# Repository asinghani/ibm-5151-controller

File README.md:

# IBM 5151 Controller

Building a VT100 emulator out of an old IBM 5151 monitor and an FPGA

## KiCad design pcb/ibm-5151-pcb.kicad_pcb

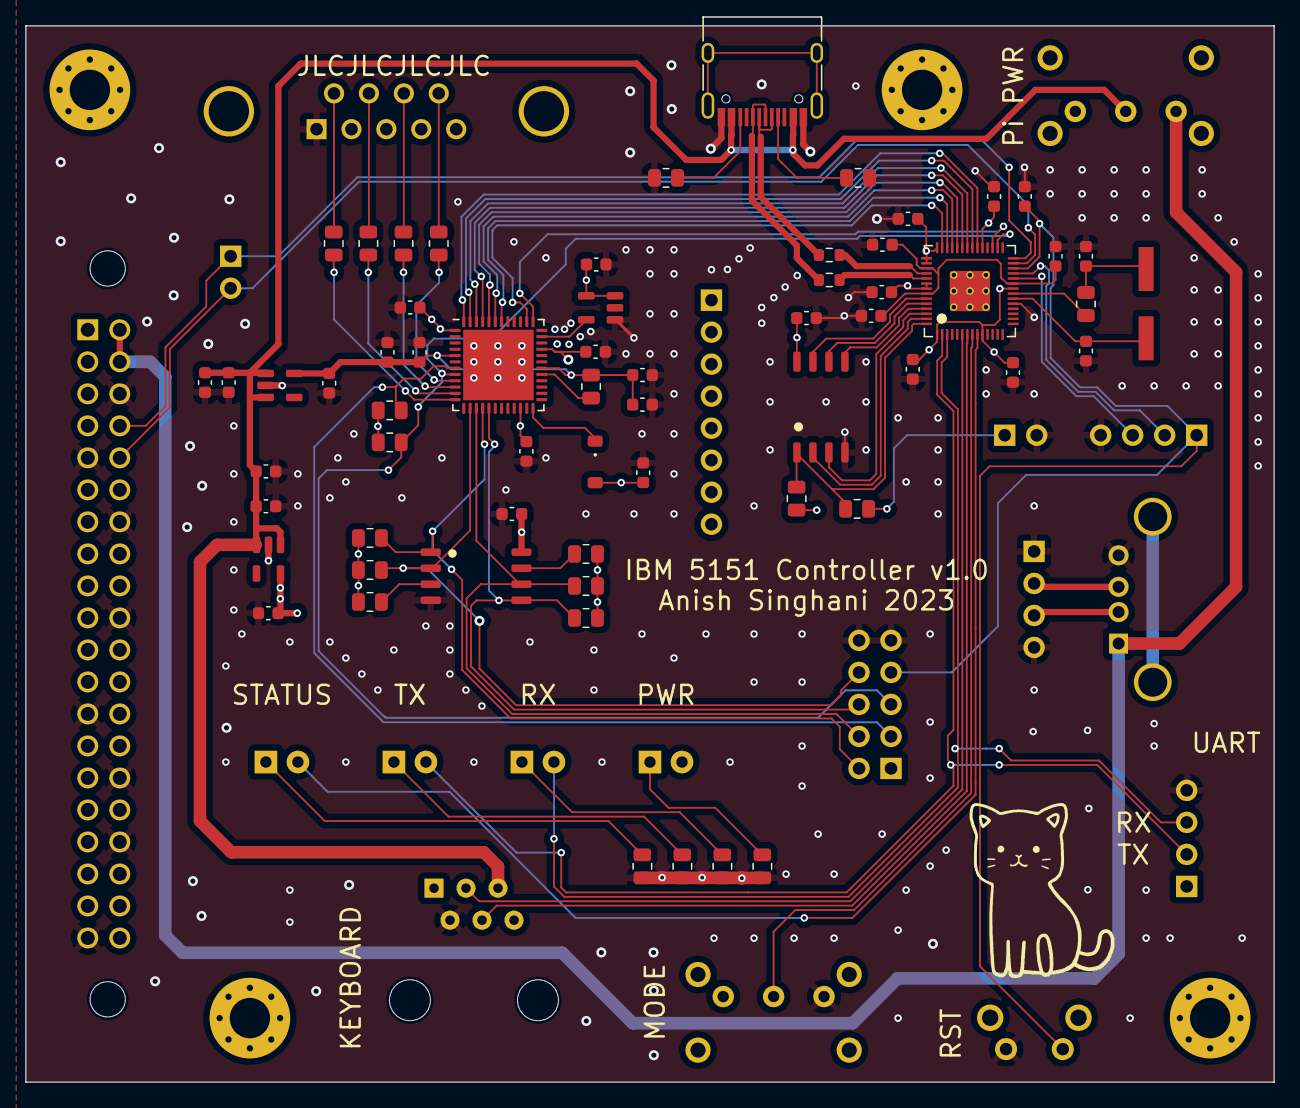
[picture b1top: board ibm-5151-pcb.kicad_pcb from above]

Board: 4 copper layers, 99.1 x 83.8 mm, 84 parts (0 on the bottom side), 67 nets.

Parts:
C1, C2, C13: 10u; C_0603_1608Metric
C3, C4, C5, C6, C22, C26: 1u; C_0603_1608Metric
C7, C8, C9, C10, C11, C12, C15, C16, C20, C21, C23, C24, C25, C27, C28: 100n; C_0603_1608Metric
C14: 10n; C_0603_1608Metric
C17, C18: 27p; C_0603_1608Metric
C19: 0.1u; C_0603_1608Metric
D1: MBR130; D_SOD-123
D2: RXLED; LED_D5.0mm
D3: TXLED; LED_D5.0mm
D4: STLED; LED_D5.0mm
D5: PWRLED; LED_D5.0mm
H1, H2, H3, H4: MountingHole; MountingHole_3.2mm_M3_Pad_Via
IC1: Raspberry Pi Zero W; RASPBERRYPIZEROWV13
J2: USB_USER; USB_C_Receptacle_HRO_TYPE-C-31-M-12
J3: BOOT; PinHeader_1x02_P2.54mm_Vertical
J4: RP_DEBUG; PinHeader_1x04_P2.54mm_Vertical
J5: FPGA_IF_TP; PinHeader_1x08_P2.54mm_Vertical
J6: UART_HDR; PinSocket_1x04_P2.54mm_Horizontal
J7: KBD_CONN; RJ12_Amphenol_54601
J8: DE9_Receptacle; DSUB-9_Female_Horizontal_P2.77x2.84mm_EdgePinOffset7.70mm_H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
J9: NET_DBG; PinHeader_1x02_P2.54mm_Vertical
J10: USB_A; USB_A_Molex_67643_Horizontal
J11: USB_HDR; PinHeader_1x04_P2.54mm_Vertical
J12: FPGA_DEBUG; PinHeader_2x05_P2.54mm_Vertical
R1, R2, R3, R4, R5, R6: 10K; R_0805_2012Metric
R7, R8: 2K2; R_0805_2012Metric
R9, R21, R22, R23: 10R; R_0805_2012Metric
R10, R11: 5K1; R_0805_2012Metric
R12, R14, R17, R18, R19, R20: 1k; R_0805_2012Metric
R13: 10k, DNF; R_0805_2012Metric
R15, R16: 27R; R_0603_1608Metric
R24: 100R; R_0805_2012Metric
SW1: RP_RST; SW_Tactile_SPST_Angled_PTS645Vx58-2LFS
SW2, SW3: SW_SPDT; SW_E-Switch_EG1224_SPDT_Angled
U1: MIC5504-1.2YM5; SOT-23-5
U2: MIC5504-3.3YM5; SOT-23-5
U3: W25Q32JVSS; SOIC-8_5.23x5.23mm_P1.27mm
U4: W25Q128JVS; SOIC-8_5.23x5.23mm_P1.27mm
U5: ICE40UP5K-SG48ITR; QFN-48-1EP_7x7mm_P0.5mm_EP5.6x5.6mm
U6: RP2040; RP2040-QFN-56
X1: SiT2001BI-S2-33E-12.000000G; SOT-23-5
Y1: ECS-120-20-3X-TR; XTAL_ECS-120-20-3X-TR

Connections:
+1V2: C5.1, C12.1, C13.1, C14.1, C15.1, R24.2, U1.5 (VOUT), U5.5 (VCC), U5.30 (VCC)
+3V3: C6.1, C7.2, C8.1, C9.1, C10.1, C11.1, C16.1, C23.1, C24.1, C25.1, C26.1, C27.1, C28.2, D1.2 (A), D5.2 (A), J6.1, J12.1, R1.1, R2.1, R3.1, R4.1, R5.1, R6.1, R7.1, R8.1, R13.1, SW2.1 (A), U2.5 (VOUT), U3.8 (VCC), U4.8 (VCC), U5.1 (VCCIO_2), U5.22 (SPI_VCCIO1), U5.33 (VCCIO_0), U6.1 (IOVDD), U6.10 (IOVDD), U6.22 (IOVDD), U6.33 (IOVDD), U6.42 (IOVDD), U6.43 (ADC_AVDD), U6.44 (VREG_IN), U6.48 (USB_VDD), U6.49 (IOVDD), X1.3 (OE), X1.4 (Vcc)
+5V: C1.1, C2.1, C3.1, C4.1, J2.A4 (VBUS), J2.A9 (VBUS), J2.B4 (VBUS), J2.B9 (VBUS), J7.5, SW3.2 (B), U1.1 (VIN), U1.3 (EN), U2.1 (VIN), U2.3 (EN)
FPGA_CSn: J12.2, R1.2, U3.1 (~CS), U5.16 (IOB_35b_SPI_SS)
FPGA_DONE: J12.3, R8.2, U5.7 (CDONE)
FPGA_IF_0: J5.1, U5.48 (IOB_4a), U6.34 (GPIO22)
FPGA_IF_1: J5.2, U5.47 (IOB_2a), U6.35 (GPIO23)
FPGA_IF_2: J5.3, U5.46 (IOB_0a), U6.36 (GPIO24)
FPGA_IF_3: J5.4, U5.45 (IOB_5b), U6.37 (GPIO25)
FPGA_IF_4: J5.5, U5.44 (IOB_3b_G6), U6.38 (GPIO26_ADC0)
FPGA_IF_5: J5.6, U5.43 (IOT_49a), U6.39 (GPIO27_ADC1)
FPGA_IF_6: J5.7, U5.42 (IOT_51a), U6.40 (GPIO28_ADC2)
FPGA_IF_7: J5.8, U5.38 (IOT_50b), U6.41 (GPIO29_ADC3)
FPGA_IF_RST: U5.37 (IOT_45a_G1), U6.31 (GPIO20)
FPGA_MISO: J12.8, R4.2, U3.2 (DO(IO1)), U5.14 (IOB_32a_SPI_SO)
FPGA_MOSI: J12.6, R3.2, U3.5 (DI(IO0)), U5.17 (IOB_33b_SPI_SI)
FPGA_OSC: U5.35 (IOT_46b_G0), X1.5 (OUT)
FPGA_RSTn: J12.5, R7.2, U5.8 (~CRESET), U6.30 (GPIO19)
FPGA_SCK: J12.4, R2.2, U3.6 (CLK), U5.15 (IOB_34a_SPI_SCK)
GND: C1.2, C2.2, C3.2, C4.2, C5.2, C6.2, C7.1, C8.2, C9.2, C10.2, C11.2, C12.2, C13.2, C14.2, C15.2, C16.2, C17.2, C18.2, C19.2, C20.2, C21.2, C22.2, C23.2, C24.2, C25.2, C26.2, C27.2, C28.1, IC1.6 (GND_1), IC1.9 (GND_2), IC1.14 (GND_3), IC1.20 (GND_4), IC1.25 (GND_5), IC1.30 (GND_6), IC1.34 (GND_7), IC1.39 (GND_8), J2.A1 (GND), J2.A12 (GND), J2.B1 (GND), J2.B12 (GND), J3.2, J4.4, J6.4, J7.2, J8.1, J8.2, J10.4 (GND), J11.1, J11.4, J12.9, J12.10, R10.2, R11.2, R17.2, R18.2, R19.2, R20.2, SW1.2, SW2.3 (C), U1.2 (GND), U2.2 (GND), U3.4 (GND), U4.4 (GND), U5.49 (GND), U6.19 (TESTEN), U6.57 (GND), X1.1 (GND)
KBD_RX: J7.4, U6.7 (GPIO5)
KBD_TX: J7.3, U6.6 (GPIO4)
LED_STATUS: D4.2 (A), U6.9 (GPIO7)
NET_RX: IC1.8 (GPIO_14/[UART]_TXD0), J9.1, U6.28 (GPIO17)
NET_TX: IC1.10 (GPIO_15/[UART]_RXD0), J9.2, U6.27 (GPIO16)
unnamed: C18.1, R14.2, Y1.2
unnamed: D1.1 (K), U5.24 (VPP_2V5)
unnamed: D2.1 (K), R17.1
unnamed: D3.1 (K), R18.1
unnamed: D4.1 (K), R19.1
unnamed: D5.1 (K), R20.1
unnamed: J2.A5 (CC1), R10.1
unnamed: J2.B5 (CC2), R11.1
unnamed: J8.6, R9.2
unnamed: J8.7, R21.2
unnamed: J8.8, R22.2
unnamed: J8.9, R23.2
unnamed: J10.3 (D+), J11.2
unnamed: J10.2 (D-), J11.3
unnamed: R5.2, U3.3 (IO2)
unnamed: R6.2, U3.7 (IO3)
unnamed: R24.1, U5.29 (VCCPLL)
unnamed: R16.2, U6.46 (USB_DM)
unnamed: R15.2, U6.47 (USB_DP)
unnamed: C20.1, C21.1, C22.1, U6.23 (DVDD), U6.45 (VREG_VOUT), U6.50 (DVDD)
unnamed: C17.1, U6.20 (XIN), Y1.1
unnamed: R14.1, U6.21 (XOUT)
RP_BOOT: J3.1, R12.1
RP_CSn: R12.2, R13.2, U4.1 (~CS), U6.56 (QSPI_SS)
RP_RSTn: C19.1, J4.1, J12.7, SW1.1, U6.26 (RUN)
RP_SCK: U4.6 (CLK), U6.52 (QSPI_SCLK)
RP_SD0: U4.5 (DI(IO0)), U6.53 (QSPI_SD0)
RP_SD1: U4.2 (DO(IO1)), U6.55 (QSPI_SD1)
RP_SD2: U4.3 (IO2), U6.54 (QSPI_SD2)
RP_SD3: U4.7 (IO3), U6.51 (QSPI_SD3)
SWCLK: J4.3, U6.24 (SWCLK)
SWDIO: J4.2, U6.25 (SWD)
SW_SEL: SW2.2 (B), U6.8 (GPIO6)
UART_RX: D2.2 (A), J6.3, U6.3 (GPIO1)
UART_TX: D3.2 (A), J6.2, U6.2 (GPIO0)
USB_N: J2.A7 (D-), J2.B7 (D-), R16.1
USB_P: J2.A6 (D+), J2.B6 (D+), R15.1
USB_PWR: IC1.2 (+5V_1), IC1.4 (+5V_2), J10.1 (VBUS), SW3.1 (A)
VIDEO_HSYNC: R22.1, U5.10 (IOB_18a)
VIDEO_INTENS: R9.1, U5.12 (IOB_22a)
VIDEO_PIXEL: R21.1, U5.11 (IOB_20a)
VIDEO_VSYNC: R23.1, U5.9 (IOB_16a)

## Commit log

2023-10-15 finish pcb layout
2023-10-15 add license
2023-11-14 add initial display gateware
2023-11-14 Updates to serial memory
2023-12-21 Gateware updates, improve Scala build config
2024-01-03 Add experimental files and font generation notebook
2024-05-08 Cleanup
